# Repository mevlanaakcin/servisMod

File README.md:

# servisMod
Okul Servis Araçlarında Öğrenci Koltuk Sensör Sistemi (TSE-EMC Belgeli)
<br>
<br>
<h3>PCB Tasarımı</h3><br>
Elektronik devre şeması ve PCB board tasarımı Eagle de tasarlandı.<br>

<br>
Mikrokontrolör olarak ATMEGA2560-16U Mikrodenetleyici kullanıldı.<br>
TSE'den <strong>EMC Belgesi</strong> alınan bir projedir.<br>
Servis koltuklarında bulunan sensörlerdeki yolcunun oturup oturmadığını algılayıp, yorumlayıp bluetooth ile şoförün android cihazına aktarır. Şoför buradan koltukların durumunu takip edebilir.
Eğer herhangi bir yolcu içeride unutulursa aracın korna ve park lambaları çevreyi uyaracak şekilde çalışacaktır.

<br>
<h5>Üretilmiş, Dizgisi yapılmış ve Yazılımı yüklenip test Edilmiş Hali</h5>

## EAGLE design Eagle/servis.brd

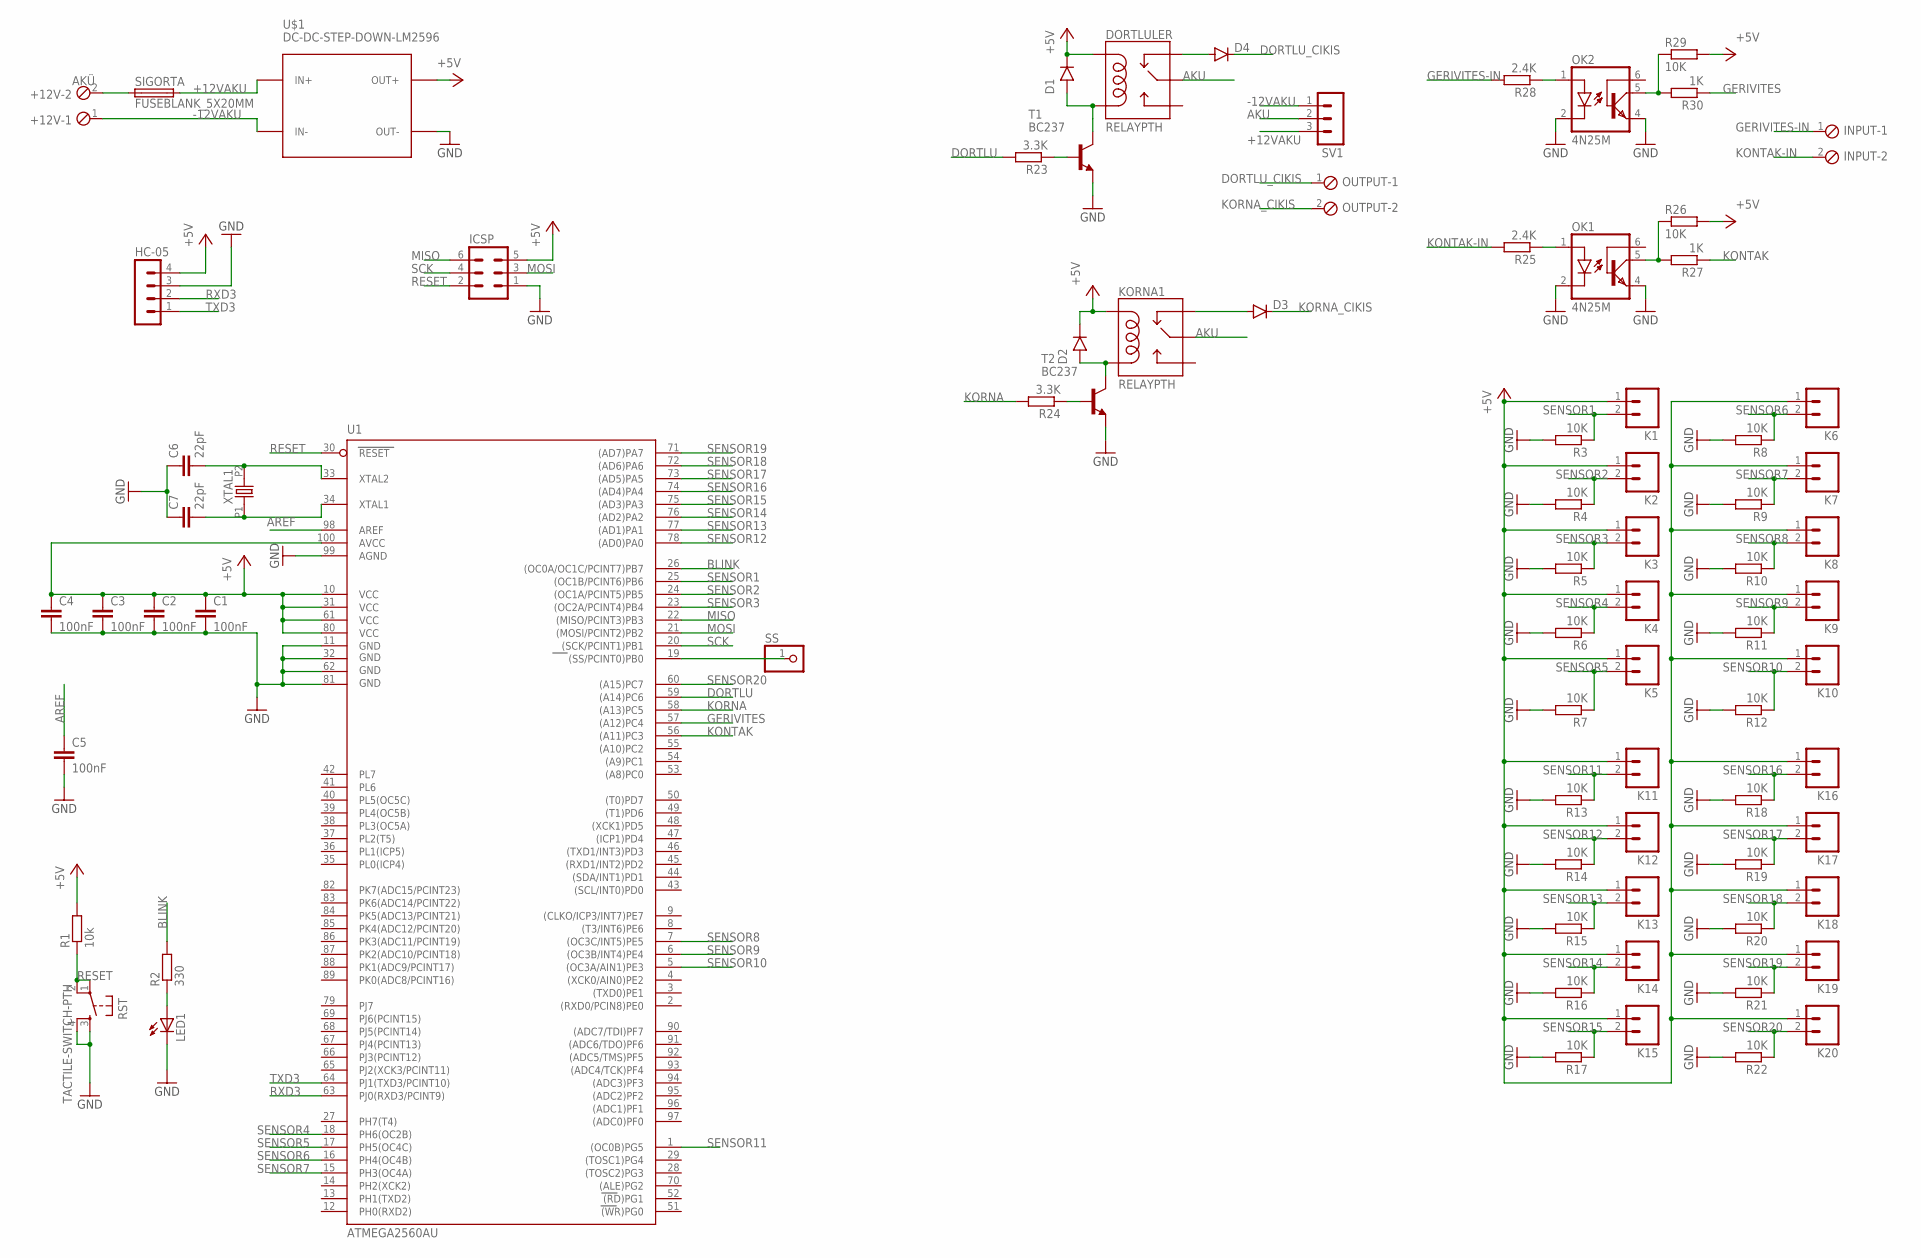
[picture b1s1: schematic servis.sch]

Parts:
+12V: AKÜ; 2POL254
C1, C2, C3, C4, C5: 100nF; SPARKFUN_0805
C6, C7: 22pF; SPARKFUN_0805
D1, D2: 1N4001; DO41-10
D3, D4: DIODEPTH; DIODE-1N4001
DORTLULER: RELAYPTH; SRD-05VDC-SL-C
HC-05: MA04-1
ICSP: MA03-2
INPUT: AKÜ; 2POL254
K1, K2, K3, K4, K5, K6, K7, K8, K9, K10, K11, K12, K13, K14, K15, K16, K17, K18, K19, K20: SPARKFUN_M02-JST-2-PTH-NO_SILK; SPARKFUN_JST-2-PTH-NS
KORNA1: RELAYPTH; SRD-05VDC-SL-C
LED1: SPARKFUN_LED3MM
OK1, OK2: 4N25M; DIL06
OUTPUT: AKÜ; 2POL254
R1: 10k; R805
R2: 330; R805
R3, R4, R5, R6, R7, R8, R9, R10, R11, R12, R13, R14, R15, R16, R17, R18, R19, R20, R21, R22, R26, R29: 10K; R805
R23, R24: 3.3K; R805
R25, R28: 2.4K; R805
R27, R30: 1K; R805
RST: TACTILE-SWITCH-PTH; TAC-SWITCH-PTH
SIGORTA: FUSEBLANK_5X20MM; FUSE_HOLDER_5X20MM
SS: PINHD-1X1; 1X01
SV1: MA03-1
T1, T2: BC237; TO92
U1: ATMEGA2560AU; TQFP100
U$1: DC-DC-STEP-DOWN-LM2596
XTAL1: OSC-XTAL-HC-49U-PTH; HC-49U-PTH

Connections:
+5V: C1.1, C2.1, C3.1, C4.1, D1.C (CATHODE), D2.C (CATHODE), DORTLULER.COIL1, HC-05.4, ICSP.5, K1.1, K2.1, K3.1, K4.1, K5.1, K6.1, K7.1, K8.1, K9.1, K10.1, K11.1, K12.1, K13.1, K14.1, K15.1, K16.1, K17.1, K18.1, K19.1, K20.1, KORNA1.COIL1, R1.2, R26.2, R29.2, U1.10 (VCC), U1.31 (VCC1), U1.61 (VCC2), U1.80 (VCC3), U1.100 (AVCC), U$1.OUT+
+12VAKU: SIGORTA.2, SV1.3, U$1.IN+
-12VAKU: +12V.1, SV1.1, U$1.IN-
AKU: DORTLULER.SWCOMMON, KORNA1.SWCOMMON, SV1.2
AREF: C5.1, U1.98 (AREF)
BLINK: R2.2, U1.26 ((OC0A/OC1C/PCINT7)PB7)
DORTLU: R23.2, U1.59 ((A14)PC6)
DORTLU_CIKIS: D4.C, OUTPUT.1
GERIVITES: R30.1, U1.57 ((A12)PC4)
GERIVITES-IN: INPUT.1, R28.2
GND: C1.2, C2.2, C3.2, C4.2, C5.2, C6.1, C7.1, HC-05.3, ICSP.1, LED1.K (C), OK1.2 (C), OK1.4 (EMI), OK2.2 (C), OK2.4 (EMI), R3.2, R4.2, R5.2, R6.2, R7.2, R8.2, R9.2, R10.2, R11.2, R12.2, R13.2, R14.2, R15.2, R16.2, R17.2, R18.2, R19.2, R20.2, R21.2, R22.2, RST.3, RST.4, T1.1 (E), T2.1 (E), U1.11 (GND), U1.32 (GND1), U1.62 (GND2), U1.81 (GND3), U1.99 (AGND), U$1.OUT-
KONTAK: R27.1, U1.56 ((A11)PC3)
KONTAK-IN: INPUT.2, R25.2
KORNA: R24.2, U1.58 ((A13)PC5)
KORNA_CIKIS: D3.C, OUTPUT.2
KRISTAL: C6.2, U1.33 (XTAL2), XTAL1.P2 (2)
KRISTAL_2: C7.2, U1.34 (XTAL1), XTAL1.P1 (1)
MISO: ICSP.6, U1.22 ((MISO/PCINT3)PB3)
MOSI: ICSP.3, U1.21 ((MOSI/PCINT2)PB2)
unnamed: R23.1, T1.2 (B)
unnamed: D3.A, KORNA1.SWCLOSED (SWCLOSE)
unnamed: D4.A, DORTLULER.SWCLOSED (SWCLOSE)
unnamed: LED1.A, R2.1
unnamed: SS.1, U1.19 ((SS/PCINT0)PB0)
unnamed: R24.1, T2.2 (B)
unnamed: D1.A (ANODE), DORTLULER.COIL0, T1.3 (C)
unnamed: D2.A (ANODE), KORNA1.COIL0, T2.3 (C)
unnamed: OK1.1 (A), R25.1
unnamed: OK1.5 (COL), R26.1, R27.2
unnamed: +12V.2, SIGORTA.1
unnamed: OK2.1 (A), R28.1
unnamed: OK2.5 (COL), R29.1, R30.2
RESET: ICSP.2, R1.1, RST.1, RST.2, U1.30 (RESET)
RXD3: HC-05.2, U1.63 (PJ0(RXD3/PCINT9))
SCK: ICSP.4, U1.20 ((SCK/PCINT1)PB1)
SENSOR1: K1.2, R3.1, U1.25 ((OC1B/PCINT6)PB6)
SENSOR2: K2.2, R4.1, U1.24 ((OC1A/PCINT5)PB5)
SENSOR3: K3.2, R5.1, U1.23 ((OC2A/PCINT4)PB4)
SENSOR4: K4.2, R6.1, U1.18 (PH6(OC2B))
SENSOR5: K5.2, R7.1, U1.17 (PH5(OC4C))
SENSOR6: K6.2, R8.1, U1.16 (PH4(OC4B))
SENSOR7: K7.2, R9.1, U1.15 (PH3(OC4A))
SENSOR8: K8.2, R10.1, U1.7 ((OC3C/INT5)PE5)
SENSOR9: K9.2, R11.1, U1.6 ((OC3B/INT4)PE4)
SENSOR10: K10.2, R12.1, U1.5 ((OC3A/AIN1)PE3)
SENSOR11: K11.2, R13.1, U1.1 ((OC0B)PG5)
SENSOR12: K12.2, R14.1, U1.78 ((AD0)PA0)
SENSOR13: K13.2, R15.1, U1.77 ((AD1)PA1)
SENSOR14: K14.2, R16.1, U1.76 ((AD2)PA2)
SENSOR15: K15.2, R17.1, U1.75 ((AD3)PA3)
SENSOR16: K16.2, R18.1, U1.74 ((AD4)PA4)
SENSOR17: K17.2, R19.1, U1.73 ((AD5)PA5)
SENSOR18: K18.2, R20.1, U1.72 ((AD6)PA6)
SENSOR19: K19.2, R21.1, U1.71 ((AD7)PA7)
SENSOR20: K20.2, R22.1, U1.60 ((A15)PC7)
TXD3: HC-05.1, U1.64 (PJ1(TXD3/PCINT10))

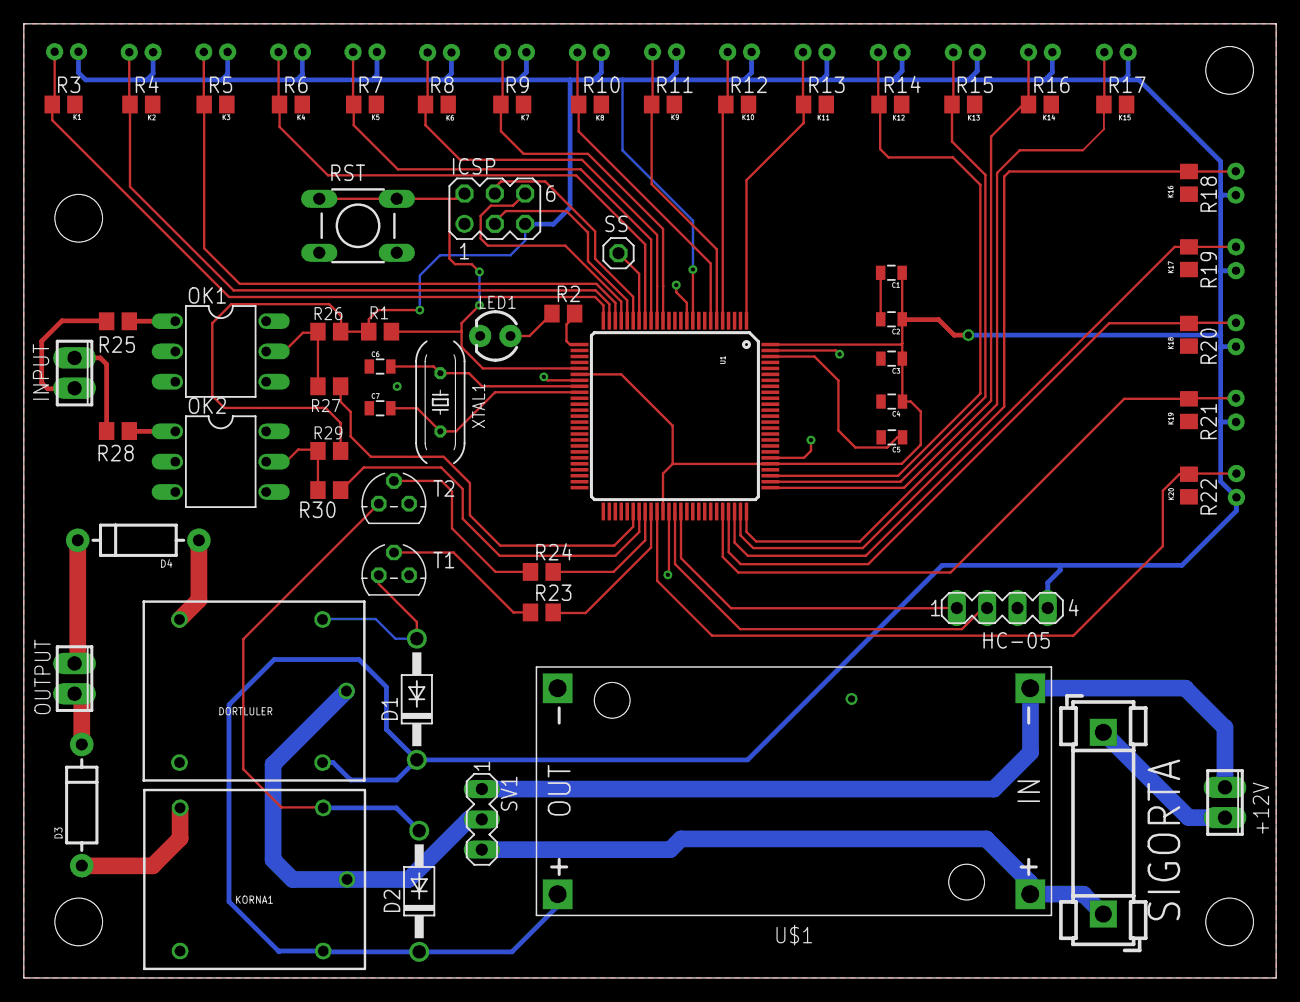
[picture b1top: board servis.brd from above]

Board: 2 copper layers, 105.0 x 80.0 mm, 80 parts (0 on the bottom side), 56 nets.

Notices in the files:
parts and their libraries:
DECADE-libraries20151104: Licensing: Creative Commons ShareAlike 4.0 International - https://creativecommons.org/licenses/by-sa/4.0
diy-modules: Released under the Creative Commons Attribution 4.0 International License: http://creativecommons.org/licenses/by/4.0
